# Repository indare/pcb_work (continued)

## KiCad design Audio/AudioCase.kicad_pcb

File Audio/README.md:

# Audio（AudioCase）

KiCad プロジェクトと関連ドキュメント。

## ドキュメント案内

| ファイル | 内容 |
|---|---|
| [MeasurementADC_STATUS.md](MeasurementADC_STATUS.md) | **現状・次作業・箱内配線方針**（まずここ） |
| [MeasurementADC_BRINGUP.md](MeasurementADC_BRINGUP.md) | 初号機の切り分けログ（履歴） |
| [MeasurementADC_ORDER.md](MeasurementADC_ORDER.md) | 発注・在庫 |
| [measurement_fw/README.md](measurement_fw/README.md) | 計測 Pico2 ファーム |
| [../Control/README.md](../Control/README.md) | Controll 親／子ファーム |
| [../README.md](../README.md) | リポジトリ全体・KiCad MCP |

## 階層シート

| シート | 役割 | いまの扱い |
|---|---|---|
| PowerModule | **DKMW20F-15** ±15 / ±660mA（1″×1″。TMR 6 は電流不足の次点）。計算メモ: [PowerModule_TEC3_REDESIGN.md](PowerModule_TEC3_REDESIGN.md) | 箱に入れる |
| AmpModule | NE5532 Amp（×10 想定）。AMP401 は DIP-8 ソケット | ラインアウト（J11）。ADC へは AdcBuffer 経由 |
| AdcBuffer | ゲイン1バッファ。実装は **OPA1652AID-DIP**（共立 Q5M411） | Amp L/R_OUT → MeasurementADC AUDIO |
| HeadphoneBuffer | ゲイン1電流バッファ。実装は **NJM4556A**（DIP-8 ソケット） | SW101 PHONE → パッド → RV101 → バッファ → J103 |
| Controll | CH1–10 リレー（親＋子） | 実機では外している |
| MeasurementADC | 計測＋LCD | 初号応急配線で稼働 |
| EQModule | EQ | 今号では使わない |
| RVConvert | RV 変換 | 箱計画に含むかは別途 |

## 出力切り替えとヘッドホン出力

SW101（DP3T）で Amp 出力の行き先を選ぶ。中央位置はミュート。

- PHONE: `SW101` → 固定パッド `R102/R101`（L）`R104/R103`（R）→ `RV101` A50k デュアル → `HeadphoneBuffer`（`R901/R903` 10Ω → `C901/C902` 470µF）→ `J103`
- LINE: `SW101` → `RV102` A50k デュアル → `J104`
- ADC への分岐はスイッチより手前なので、切り替え位置に関係なく測定できる

固定パッドは 8.2kΩ 直列＋910Ω 並列で約 −20dB。±15V・ゲイン1では最大出力がヘッドホンに対して過大で、
ボリュームが回転下端だけで使われてしまうため入れている。不要なら直列を 0Ω、並列を未実装にすればバイパスできる。
直列と並列の位置を取り違えると分圧にならず減衰が効かないので、必ず 8.2kΩ をスイッチ側の直列、910Ω を
ポット側から GND へ落とす並列にする。

**`RV101` はバッファより前**に置く。50kΩ のポットを 32Ω のヘッドホンより後ろに置くと、
ワイパー出力インピーダンス（中点で最大約 12.5kΩ）に対して負荷が軽すぎて −50dB 級まで落ち、
回転上端の数度だけで音が出るうえヘッドホン電流が抵抗体を流れる。

`C901/C902` は 470µF の**無極性（バイポーラ）**電解。両電源で出力の直流はほぼ 0V なので極性品は使わない。
故障時にヘッドホンへ ±15V が出るのを防ぐのと、電源投入時のポップ抑制が目的。
`R902/R904` 100kΩ はヘッドホン未接続時に出力ノードを確定させるブリード。

### SW101 はパネル実装（基板側は 2x04 ヘッダ）

KiCad 標準ライブラリに 2P3T（8ピン）のフットプリントが無く、選択機はパネルから操作する部品なので、
基板側は `PinHeader_2x04_P2.54mm_Vertical` にしてパネル実装の 2P3T スイッチへリード線で引く。
`SW_DIP_SPSTx04` 系は 8 パッドあるが独立 4 回路でピン機能が違うため流用しない。

| ヘッダピン | スイッチ端子 | つながる先 |
|---|---|---|
| 3 | L 極 コモン | Amp L 出力（ADC への分岐と共通） |
| 1 | L PHONE | 固定パッド `R102` → `RV101` |
| 2 | L MUTE | 未接続 |
| 4 | L LINE | `RV102` |
| 7 | R 極 コモン | Amp R 出力 |
| 5 | R PHONE | 固定パッド `R104` → `RV101` |
| 6 | R MUTE | 未接続 |
| 8 | R LINE | `RV102` |

## AdcBuffer の入力極性

`AMP801` は**上下反転で描いてある**（− 入力が上、+ 入力が下）。信号は `R804/R809` 0Ω で **+ 入力**へ入り、
`R805/R810` 100kΩ が + 入力のバイアスプルダウン、帰還は `R801/R806` 0Ω で **− 入力**へ戻り、
`R803/R808` 10kΩ が − 入力の Rg。Rf=0Ω なのでゲインは 1。

反転を戻して + と − を入れ替えると帰還が + 入力に回って正帰還になり、出力が電源レールに張り付く。
シンボルの向きだけで極性が決まるので、このシートを編集したら `Net-(AMP801A-+)` に `R804`/`R805` が、
`Net-(AMP801A--)` に `R801`/`R803` が入っていることをネットリストで確認する。

## オペアンプソケットの差し替え

3 か所すべて DIP-8 ソケットだが、役割が違うので入れられる品種が違う。**取り違えると壊す。**  
手持ち在庫の一覧は **[OPAMP_INVENTORY.md](OPAMP_INVENTORY.md)**。

| ソケット | 役割 | 標準 | 差し替え | 制約 |
|---|---|---|---|---|
| `AMP401`（AmpModule） | 電圧増幅 ×10（プリアンプ） | NE5532 | 手持ち DIP／DIP 化モジュール（在庫表） | 高速石は安定性注意。SOIC 単体は不可 |
| `AMP801`（AdcBuffer） | 測定系ゲイン1バッファ | OPA1652AID-DIP | 原則固定 | 測定の基準。ここを動かすと比較の土台が動く |
| `AMP901`（HeadphoneBuffer） | ヘッドホン電流ドライバ | NJM4556A | **不可** | 32Ω 直接駆動が必要。電圧アンプ系は電流不足 |

`AMP401` の出力は AdcBuffer 経由で測定 ADC にも、SW101 経由でヘッドホン／ラインにも行く。
つまりここを差し替えると、聴いている音と測っている波形が同じ変化を受ける。比較実験はこのソケットで行う。

## 分割 Gerber

`split/Gerber/` — `01_main` … `06_measurement_adc`。再生成は `scripts/regenerate_split_gerbers.py`。

## S式の健全性チェック

回路図・基板ファイルをテキスト編集したら `python3 scripts/check_sexpr.py -q .` で括弧の対応を確認する。
既知の壊れ方（`property` の閉じ括弧が早い）は `--fix` で直せる。手順は [`.cursor/rules/kicad-sexpr-integrity.mdc`](../.cursor/rules/kicad-sexpr-integrity.mdc)。

コミット時にも同じ検査が走る。クローン直後は一度だけ有効化が必要。

```bash
git config core.hooksPath .githooks
```

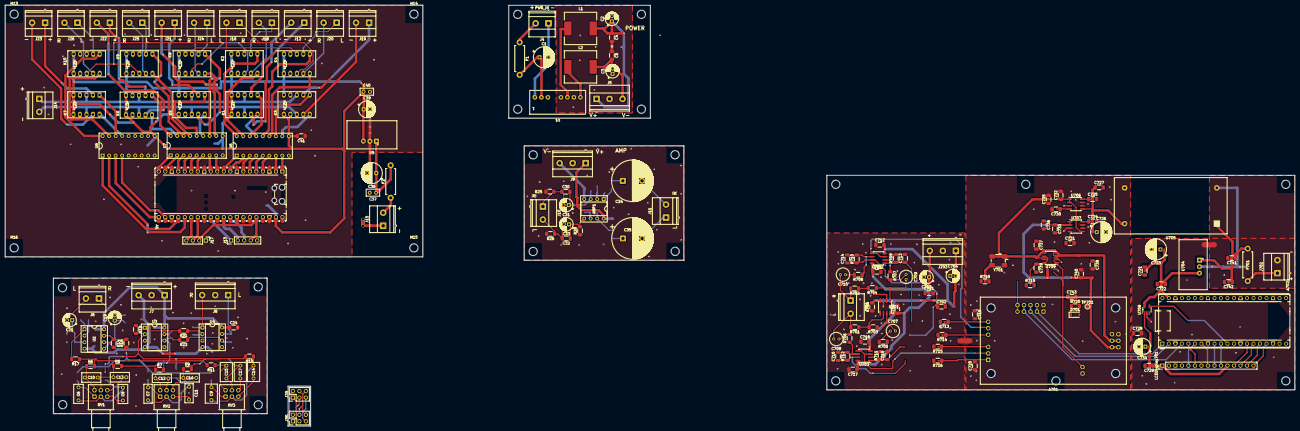
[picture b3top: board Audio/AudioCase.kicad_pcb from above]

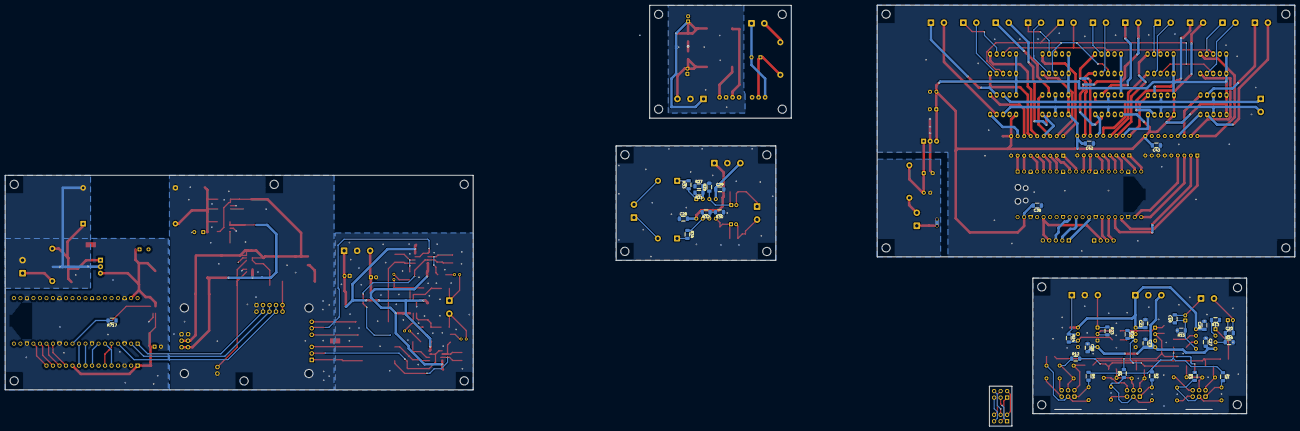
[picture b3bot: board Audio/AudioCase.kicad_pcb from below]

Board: 2 copper layers, 503.2 x 164.2 mm, 236 parts (32 on the bottom side), 185 nets.

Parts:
A1: RaspberryPi_Pico; RaspberryPi_Pico_Common_Unspecified
A701: ADC1804_F_MODULE; ADC1804_F_KYOHRITSU_56x33mm
A702: Pico2; RaspberryPi_Pico_Common_THT
AMP1: NE5532; DIP-8_W7.62mm_Socket
C1, C36: 47μF; CP_Radial_D8.0mm_P3.50mm
C2, C3: 4.7μF; CP_Radial_D5.0mm_P2.00mm
C4, C5, C18, C20, C22, C23, C24, C25, C26, C27, C28, C29, C30, C32, C38, C41, C42, C43: 0.1μF; C_1206_3216Metric_Pad1.33x1.80mm_HandSolder
C6, C8, C10, C13: 0.047μF; C_Rect_L7.2mm_W3.5mm_P5.00mm_FKS2_FKP2_MKS2_MKP2
C7, C11, C12, C16: 0.01uF; C_Rect_L7.2mm_W3.0mm_P5.00mm_FKS2_FKP2_MKS2_MKP2
C9, C14, C15, C17: 2200pF; C_Rect_L7.2mm_W4.5mm_P5.00mm_FKS2_FKP2_MKS2_MKP2
C19, C21, C31, C33: 10μF; CP_Radial_D5.0mm_P2.00mm
C34, C35: 470μF; CP_Radial_D16.0mm_P7.50mm
C37, C40: 0.1μF; C_Disc_D5.0mm_W2.5mm_P2.50mm
C39: 100μF; CP_Radial_D6.3mm_P2.50mm
C701, C702, C705, C706, C711, C712, C717, C718, C719, C720, C721, C722, C725, C727, C729, C730, C733, C740, C741, C743: 100nF; C_1206_3216Metric_Pad1.33x1.80mm_HandSolder
C703, C704: 10uF 50V; CP_Radial_D5.0mm_P2.00mm
C707, C708, C709, C710: 10uF 25V NP; C_Radial_D5.0mm_H7.0mm_P2.00mm
C713, C714, C715, C716: 1.8nF C0G; C_1206_3216Metric_Pad1.33x1.80mm_HandSolder
C723: 47uF 35V; CP_Radial_D8.0mm_P3.50mm
C724, C728, C739: 10uF; C_1206_3216Metric_Pad1.33x1.80mm_HandSolder
C726: 47uF; CP_Radial_D8.0mm_P3.50mm
C731, C732, C738: 10uF 16V X7R; C_1206_3216Metric_Pad1.33x1.80mm_HandSolder
C734: 22uF; CP_Radial_D6.3mm_P2.50mm
C735, C736, C742: 10nF; C_1206_3216Metric_Pad1.33x1.80mm_HandSolder
C737: 10uF 10V X7R; C_1206_3216Metric_Pad1.33x1.80mm_HandSolder
D701: RB160M-30; D_SOD-123
F1, F2: 1A; R_Axial_DIN0411_L9.9mm_D3.6mm_P12.70mm_Horizontal
F701: Fuse; R_Axial_DIN0411_L9.9mm_D3.6mm_P12.70mm_Horizontal
H1, H2, H3, H4, H5, H6, H7, H8, H9, H10, H11, H11#2, H11#3, H11#4, H11#5, H11#6, H11#7, H12, H13, H14, H15, H16: MountingHole; MountingHole_3.2mm_M3
J4: PWR_IN; TerminalBlock_Phoenix_MKDS-1,5-2_1x02_P5.00mm_Horizontal
J5: PWR_OUT; TerminalBlock_Phoenix_MKDS-1,5-3-5.08_1x03_P5.08mm_Horizont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
J6: AUX_IN; TerminalBlock_Phoenix_MKDS-1,5-2-5.08_1x02_P5.08mm_Horizont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
J7: V_IN; TerminalBlock_Phoenix_MKDS-1,5-3-5.08_1x03_P5.08mm_Horizont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
J8: AUX_OUT; TerminalBlock_Phoenix_MKDS-1,5-3-5.08_1x03_P5.08mm_Horizont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
J9: AMP_PWR; TerminalBlock_Phoenix_MKDS-1,5-3-5.08_1x03_P5.08mm_Horizont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
J10: AMP_AUX_IN; TerminalBlock_Phoenix_MKDS-1,5-2-5.08_1x02_P5.08mm_Horizont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
J11: AMP_AUX_OUT; TerminalBlock_Phoenix_MKDS-1,5-2-5.08_1x02_P5.08mm_Horizont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
J12: AMP1_PWR; TerminalBlock_Phoenix_MKDS-1,5-2-5.08_1x02_P5.08mm_Horizont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
J13: ROTARY_SW; PinHeader_1x05_P2.54mm_Vertical
J14: AMP_PWR_IN; TerminalBlock_Phoenix_MKDS-1,5-2-5.08_1x02_P5.08mm_Horizont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
J15: PD_IN; TerminalBlock_Phoenix_MKDS-1,5-2-5.08_1x02_P5.08mm_Horizont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
J16: AUDIO_IN; TerminalBlock_Phoenix_MKDS-1,5-2-5.08_1x02_P5.08mm_Horizont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
J17: OLED_PIN; PinHeader_1x04_P2.54mm_Vertical
J18: AMP1_LR; TerminalBlock_Phoenix_MKDS-1,5-2-5.08_1x02_P5.08mm_Horizont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
J19: AMP2_PWR; TerminalBlock_Phoenix_MKDS-1,5-2-5.08_1x02_P5.08mm_Horizont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
J20: AMP2_LR; TerminalBlock_Phoenix_MKDS-1,5-2-5.08_1x02_P5.08mm_Horizont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
J21: AMP3_PWR; TerminalBlock_Phoenix_MKDS-1,5-2-5.08_1x02_P5.08mm_Horizont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
J22: AMP4_PWR; TerminalBlock_Phoenix_MKDS-1,5-2-5.08_1x02_P5.08mm_Horizont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
J23: AMP5_PWR; TerminalBlock_Phoenix_MKDS-1,5-2-5.08_1x02_P5.08mm_Horizont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
J24: AMP3_LR; TerminalBlock_Phoenix_MKDS-1,5-2-5.08_1x02_P5.08mm_Horizont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
J25: AMP4_LR; TerminalBlock_Phoenix_MKDS-1,5-2-5.08_1x02_P5.08mm_Horizont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
J26: AMP5_LR; TerminalBlock_Phoenix_MKDS-1,5-2-5.08_1x02_P5.08mm_Horizont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
J29, J30: Conn_01x06_Pin; PinHeader_2x03_P2.54mm_Vertical
J701: AUDIO; TerminalBlock_Phoenix_MKDS-1,5-2-5.08_1x02_P5.08mm_Horizont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
J702: V_IN; TerminalBlock_Phoenix_MKDS-1,5-2-5.08_1x02_P5.08mm_Horizont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
J703: 15_V_IN; TerminalBlock_Phoenix_MKDS-1,5-3-5.08_1x03_P5.08mm_Horizont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
K1, K2, K3, K4, K5, K6, K7, K8, K9, K10: AZ850P2-x; Relay_DPDT_FRT5
L1, L2: L; L_12x12mm_H8mm
LCDDisplay701: WAVESHARE-29318; PinHeader_1x15_P2.54mm_Vertical
NT1: NetTie_2; NetTie-2_THT_Pad1.0mm
NT701: A_GND-ADC_GND; NetTie-2_SMD_Pad2.0mm
NT702: ADC_GND_IN-D_GND; NetTie-2_SMD_Pad2.0mm
R1, R2, R3, R4, R5, R6, R7, R8, R9, R10, R11, R12: 10K; R_1206_3216Metric_Pad1.30x1.75mm_HandSolder
R13, R14: 0Ω; R_1206_3216Metric_Pad1.30x1.75mm_HandSolder
R15, R16: 47kΩ; R_1206_3216Metric_Pad1.30x1.75mm_HandSolder
R17, R18, R33, R34: 47Ω; R_1206_3216Metric_Pad1.30x1.75mm_HandSolder
R19, R20, R27, R28, R29, R30: 10KΩ; R_1206_3216Metric_Pad1.30x1.75mm_HandSolder
R21, R22, R23, R24: 22KΩ; R_1206_3216Metric_Pad1.30x1.75mm_HandSolder
R25, R26: 220KΩ; R_1206_3216Metric_Pad1.30x1.75mm_HandSolder
R31, R32: 47KΩ; R_1206_3216Metric_Pad1.30x1.75mm_HandSolder
R701, R702, R703, R704: 4.7k 0.1%; R_1206_3216Metric_Pad1.30x1.75mm_HandSolder
R705, R706, R707, R708: 3.3k 0.1%; R_1206_3216Metric_Pad1.30x1.75mm_HandSolder
R709, R710, R711, R712: 1k 0.1%; R_1206_3216Metric_Pad1.30x1.75mm_HandSolder
R713, R714, R715, R716: 47; R_1206_3216Metric_Pad1.30x1.75mm_HandSolder
R717: 100k; R_1206_3216Metric_Pad1.30x1.75mm_HandSolder
R718: 33; R_1206_3216Metric_Pad1.30x1.75mm_HandSolder
R719: 10k; R_1206_3216Metric_Pad1.30x1.75mm_HandSolder
R720: 1k; R_1206_3216Metric_Pad1.30x1.75mm_HandSolder
RV1, RV2, RV3: B100k_Dual; Potentiometer_Alps_RK097_Dual_Horizontal
TP701: ADC_MCLK; TestPoint_Pad_D1.5mm
U1: MCW03; MCW03-12D15_SIP7_THT
U2, U3, U4: NJM4558; DIP-8_W7.62mm_Socket
U5, U704: BP5293-50; BP5293-50_ROHM_SIP-3
U6, U7, U8: ULN2803A; ULN2803A_DIP-18_W7.62mm
U701, U702, U703: OPA1656; SOIC-8_3.9x4.9mm_P1.27mm
U705: MBC2596-01; MBC2596-01_TAEJIN_43x21mm
U706: LT1763-3.3; SOIC-8_3.9x4.9mm_P1.27mm
U707: LT1763-5; SOIC-8_3.9x4.9mm_P1.27mm
U708: XC8107AC20MR-G; SOT-23-5_HandSoldering
U709: TPS3307-33; SOIC-8_3.9x4.9mm_P1.27mm
Y701: ASFL1-12.288MHZ-EC-T; Oscillator_SMD_Abracon_ASFL-4Pin_5.0x3.2mm_HandSoldering

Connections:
/AmpModule/L_IN: C32.2, C33.2, J10.2, R26.1
/AmpModule/R_IN: C30.2, C31.2, J10.1, R25.1
/AmpModule/V+_IN: AMP1.8 (V+), C28.2, J9.1
/AmpModule/V-_IN: AMP1.4 (V-), C29.1, J9.3
/Controll/3V3: A1.36 (3V3), J13.4, J17.2
/Controll/5V_+: A1.39 (VSYS), C38.2, C39.1, C40.1, C41.2, C42.2, C43.2, K1.1, K1.10, K2.1, K2.10, K3.1, K3.10, K4.1, K4.10, K5.1, K5.10, K6.1, K6.10, K7.1, K7.10, K8.1, K8.10, K9.1, K9.10, K10.1, K10.10, U5.3 (VOUT), U6.10 (COM), U7.10 (COM), U8.10 (COM)
/Controll/+15_IN: C723.1, C724.1, C725.1, F1.1, F2.1, F701.2, J4.2, J15.2, U704.1 (VIN), U705.1 (IN+)
/Controll/AMP_1_L_OUT: J18.1, K2.7
/Controll/AMP_1_R_OUT: J18.2, K2.4
/Controll/AMP_1_V+_OUT: J12.1, K1.7
/Controll/AMP_1_V-_OUT: J12.2, K1.4
/Controll/AMP_2_L_OUT: J20.1, K4.7
/Controll/AMP_2_R_OUT: J20.2, K4.4
/Controll/AMP_2_V+_OUT: J19.1, K3.7
/Controll/AMP_2_V-_OUT: J19.2, K3.4
/Controll/AMP_3_L_OUT: J24.1, K8.7
/Controll/AMP_3_R_OUT: J24.2, K8.4
/Controll/AMP_3_V+_OUT: J21.1, K5.7
/Controll/AMP_3_V-_OUT: J21.2, K5.4
/Controll/AMP_4_L_OUT: J25.1, K9.7
/Controll/AMP_4_R_OUT: J25.2, K9.4
/Controll/AMP_4_V+_OUT: J22.1, K6.7
/Controll/AMP_4_V-_OUT: J22.2, K6.4
/Controll/AMP_5_L_OUT: J26.1, K10.7
/Controll/AMP_5_R_OUT: J26.2, K10.4
/Controll/AMP_5_V+_OUT: J23.1, K7.7
/Controll/AMP_5_V-_OUT: J23.2, K7.4
/Controll/AMP_V+_IN: C2.1, C4.1, C22.1, C24.1, C26.1, C701.1, C703.1, C705.1, C711.1, C717.1, J5.1, J7.1, J14.1, J703.3, K1.8, K3.8, K5.8, K6.8, K7.8, L1.1, U2.8 (V+), U3.8 (V+), U4.8 (V+), U701.8 (V+), U702.8 (V+), U703.8 (V+)
/Controll/AMP_V-_IN: C3.2, C5.2, C23.2, C25.2, C27.2, C702.2, C704.2, C706.2, C712.2, C718.2, J5.3, J7.3, J14.2, J703.1, K1.3, K3.3, K5.3, K6.3, K7.3, L2.2, U2.4 (V-), U3.4 (V-), U4.4 (V-), U701.4 (V-), U702.4 (V-), U703.4 (V-)
/Controll/AUDIO_RESET_GPIO_1: A1.2 (GPIO1), U6.7 (I7)
/Controll/AUDIO_RESET_GPIO_2: A1.7 (GPIO5), U6.3 (I3)
/Controll/AUDIO_RESET_GPIO_3: A1.12 (GPIO9), U7.7 (I7)
/Controll/AUDIO_RESET_GPIO_4: A1.17 (GPIO13), U7.3 (I3)
/Controll/AUDIO_RESET_GPIO_5: A1.24 (GPIO18), U8.1 (I1)
/Controll/AUDIO_RESET_RELAY_1: K2.6, U6.18 (O1)
/Controll/AUDIO_RESET_RELAY_2: K4.6, U6.14 (O5)
/Controll/AUDIO_RESET_RELAY_3: K8.6, U7.12 (O7)
/Controll/AUDIO_RESET_RELAY_4: K9.6, U7.16 (O3)
/Controll/AUDIO_RESET_RELAY_5: K10.6, U8.18 (O1)
/Controll/AUDIO_SET_GPIO_1: A1.1 (GPIO0), U6.8 (I8)
/Controll/AUDIO_SET_GPIO_2: A1.6 (GPIO4), U6.4 (I4)
/Controll/AUDIO_SET_GPIO_3: A1.11 (GPIO8), U7.8 (I8)
/Controll/AUDIO_SET_GPIO_4: A1.16 (GPIO12), U7.4 (I4)
/Controll/AUDIO_SET_GPIO_5: A1.25 (GPIO19), U8.2 (I2)
/Controll/AUDIO_SET_RELAY_1: K2.5, U6.17 (O2)
/Controll/AUDIO_SET_RELAY_2: K4.5, U6.13 (O6)
/Controll/AUDIO_SET_RELAY_3: K8.5, U7.11 (O8)
/Controll/AUDIO_SET_RELAY_4: K9.5, U7.15 (O4)
/Controll/AUDIO_SET_RELAY_5: K10.5, U8.17 (O2)
/Controll/CTRL_GND: A1.3 (GND), A1.8 (GND), A1.13 (GND), A1.18 (GND), A1.23 (GND), A1.28 (GND), A1.38 (GND), C36.2, C37.2, C38.1, C39.2, C40.2, C41.1, C42.1, C43.1, J13.5, J17.1, NT1.2, U5.2 (GND), U6.9 (GND), U7.9 (GND), U8.5 (I5), U8.6 (I6), U8.7 (I7), U8.8 (I8), U8.9 (GND)
/Controll/ENC_A: A1.29 (GPIO22), J13.1
/Controll/ENC_B: A1.31 (GPIO26_ADC0), J13.2
/Controll/ENC_SW: A1.32 (GPIO27_ADC1), J13.3
/Controll/L_IN: J8.1, J16.2, K2.8, K4.8, K8.8, K9.8, K10.8, R24.1, U4.7
/Controll/PWR_RESET_GPIO_1: A1.5 (GPIO3), U6.5 (I5)
/Controll/PWR_RESET_GPIO_2: A1.10 (GPIO7), U6.1 (I1)
/Controll/PWR_RESET_GPIO_3: A1.15 (GPIO11), U7.5 (I5)
/Controll/PWR_RESET_GPIO_4: A1.20 (GPIO15), U7.1 (I1)
/Controll/PWR_RESET_GPIO_5: A1.21 (GPIO16), U8.3 (I3)
/Controll/PWR_RESET_RELAY_1: K1.6, U6.16 (O3)
/Controll/PWR_RESET_RELAY_2: K3.6, U6.12 (O7)
/Controll/PWR_RESET_RELAY_3: K5.6, U7.14 (O5)
/Controll/PWR_RESET_RELAY_4: K6.6, U7.18 (O1)
/Controll/PWR_RESET_RELAY_5: K7.6, U8.16 (O3)
/Controll/PWR_SET_GPIO_1: A1.4 (GPIO2), U6.6 (I6)
/Controll/PWR_SET_GPIO_2: A1.9 (GPIO6), U6.2 (I2)
/Controll/PWR_SET_GPIO_3: A1.14 (GPIO10), U7.6 (I6)
/Controll/PWR_SET_GPIO_4: A1.19 (GPIO14), U7.2 (I2)
/Controll/PWR_SET_GPIO_5: A1.22 (GPIO17), U8.4 (I4)
/Controll/PWR_SET_RELAY_1: K1.5, U6.15 (O4)
/Controll/PWR_SET_RELAY_2: K3.5, U6.11 (O8)
/Controll/PWR_SET_RELAY_3: K5.5, U7.13 (O6)
/Controll/PWR_SET_RELAY_4: K6.5, U7.17 (O2)
/Controll/PWR_SET_RELAY_5: K7.5, U8.15 (O4)
/Controll/R_IN: J8.3, J16.1, K2.3, K4.3, K8.3, K9.3, K10.3, R23.1, U4.1
/Controll/SCL: A1.27 (GPIO21), J17.3
/Controll/SDA: A1.26 (GPIO20), J17.4
/EQModule/L_BAX_SUM: R8.2, R9.2, R12.2, R20.2, U3.6 (-)
/EQModule/L_BUFF: R6.2, R7.2, R11.2, R17.1
/EQModule/L_BUFF_IN: C20.1, C21.1, R16.1, U2.3 (+)
/EQModule/L_IN: C20.2, C21.2, J6.2
/EQModule/R_BAX_SUM: R3.2, R4.2, R10.2, R19.2, U3.2 (-)
/EQModule/R_BUFF: R1.1, R2.1, R5.1, R18.1
/EQModule/R_BUFF_IN: C18.1, C19.1, R15.1, U2.5 (+)
/EQModule/R_IN: C18.2, C19.2, J6.1
/MeasurementADC/+3V3_A: A701.13 (+3V3), C722.2, C737.1, C740.1, C742.2, C743.1, R719.1, U706.1 (OUT), U706.2 (SENSE), U707.5 (SHDN), U709.2 (SENSE2), U709.3 (SENSE3), U709.8 (VDD), Y701.1 (ST), Y701.4 (VDD)
/MeasurementADC/+5V_A: A701.12 (+5V), C721.1, C738.1, C741.1, U707.1 (OUT), U707.2 (SENSE), U709.1 (SENSE1)
/MeasurementADC/+5V_D: C726.1, C727.1, C728.1, D701.2 (A), U704.3 (VOUT), U708.5 (VIN)
/MeasurementADC/ADC_BCK: A701.9 (BCK), A702.2 (GPIO1)
/MeasurementADC/ADC_DATA: A701.10 (DATA), A702.1 (GPIO0)
/MeasurementADC/ADC_GND: A701.14 (GND), C719.1, C720.1, C721.2, C722.1, C729.2, C730.2, C731.2, C732.2, C735.2, C736.2, C737.2, C738.2, C740.2, C741.2, C742.1, C743.2, NT701.1, U705.4 (OUT-), U706.3 (GND), U706.6 (GND), U706.7 (GND), U707.3 (GND), U707.6 (GND), U707.7 (GND), U709.4 (GND), Y701.2 (GND)
/MeasurementADC/ADC_GND_IN: C1.2, C723.2, C724.2, C725.2, J4.1, J15.1, J702.2, NT1.1, NT702.1, U1.1 (GND), U704.2 (GND), U705.2 (IN-)
/MeasurementADC/ADC_LRCK: A701.8 (LRCK), A702.4 (GPIO2)
/MeasurementADC/ADC_MCLK: A701.7 (SCKI), R718.2, R720.1, TP701.1 (1_1)
/MeasurementADC/ADC_nMR: A702.20 (GPIO15), U709.7 (~MR)
/MeasurementADC/ADC_nRST: A701.11 (RST), R719.2, U709.5 (~RESET)
/MeasurementADC/AUDIO_L_IN: C35.2, C708.2, J11.1, J701.2, R701.2
/MeasurementADC/AUDIO_R_IN: C34.2, C710.2, J11.2, J701.1, R702.2
/MeasurementADC/D_GND: A702.3 (GND), A702.8 (GND), A702.13 (GND), A702.18 (GND), A702.23 (GND), A702.28 (GND), A702.38 (GND), C726.2, C727.2, C728.2, C733.1, C734.2, C739.2, LCDDisplay701.3 (GND), NT702.2, R717.2, U708.2 (VSS)
/MeasurementADC/LCD_CS: A702.7 (GPIO5), LCDDisplay701.8 (LCD_CS)
/MeasurementADC/LCD_DC: A702.9 (GPIO6), LCDDisplay701.9 (LCD_DC)
/MeasurementADC/LCD_EN: A702.11 (GPIO8), R717.1, U708.4 (CE)
/MeasurementADC/LCD_MOSI: A702.25 (GPIO19), LCDDisplay701.5 (MOSI)
/MeasurementADC/LCD_RST: A702.10 (GPIO7), LCDDisplay701.10 (LCD_RST)
/MeasurementADC/LCD_SCK: A702.24 (GPIO18), LCDDisplay701.6 (SCLK)
/MeasurementADC/LCD_VCC: C733.2, C734.1, C739.1, LCDDisplay701.1 (VCC), LCDDisplay701.11 (LCD_BL), U708.1 (VOUT)
/MeasurementADC/MCLK_SENSE: A702.12 (GPIO9), R720.2
/MeasurementADC/PICO_3V3: A702.30 (RUN), A702.35 (ADC_VREF), A702.36 (3V3), A702.37 (3V3_EN)
/MeasurementADC/TP_INT: A702.16 (GPIO12), LCDDisplay701.14 (TP_INT)
/MeasurementADC/TP_RST: A702.17 (GPIO13), LCDDisplay701.15 (TP_RST)
/MeasurementADC/TP_SCL: A702.15 (GPIO11), LCDDisplay701.13 (TP_SCL)
/MeasurementADC/TP_SDA: A702.14 (GPIO10), LCDDisplay701.12 (TP_SDA)
/MeasurementADC/VCOML: A701.2 (VCOML), C719.2, U703.3 (INA+), U703.5 (INB+)
/MeasurementADC/VCOMR: A701.5 (VCOMR), C720.2, U702.3 (INA+), U702.5 (INB+)
/MeasurementADC/VINL+: A701.1 (VINL+), R716.1
/MeasurementADC/VINL-: A701.3 (VINL-), R715.1
/MeasurementADC/VINR+: A701.6 (VINR+), R714.1
/MeasurementADC/VINR-: A701.4 (VINR-), R713.1
GND: C2.2, C3.1, C4.2, C5.1, C22.2, C23.1, C24.2, C25.1, C26.2, C27.1, C28.1, C29.2, C701.2, C702.1, C703.2, C704.1, C705.2, C706.1, C711.2, C712.1, C717.2, C718.1, J5.2, J7.2, J8.2, J9.2, J703.2, NT701.2, R15.2, R16.2, R25.2, R26.2, R27.1, R28.1, R29.2, R30.1, U1.7 (Common), U3.3 (+), U3.5 (+), U4.3 (+), U4.5 (+), U701.3 (INA+), U701.5 (INB+)
unnamed: A702.39 (VSYS), D701.1 (K)
unnamed: AMP1.1, R31.2, R33.1
unnamed: AMP1.7, R32.2, R34.1
unnamed: AMP1.3 (+), C30.1, C31.1, R29.1
unnamed: AMP1.2 (-), R27.2, R31.1
unnamed: AMP1.5 (+), C32.1, C33.1, R28.2
unnamed: AMP1.6 (-), R30.2, R32.1
unnamed: C6.1, R1.2, RV1.1
unnamed: C6.2, C8.1, R3.1, RV1.2
unnamed: C7.1, R2.2, RV2.1
unnamed: C8.2, RV1.3
unnamed: C9.1, R5.2, RV3.1
unnamed: C10.1, C13.2, R8.1, RV1.5
unnamed: C10.2, R6.1, RV1.4
unnamed: C7.2, C11.1, R4.1, RV2.2
unnamed: C11.2, RV2.3
unnamed: C12.1, C16.1, R9.1, RV2.5
unnamed: C12.2, R7.1, RV2.4
unnamed: C13.1, RV1.6
unnamed: C9.2, C14.1, R10.1, RV3.2
unnamed: C14.2, RV3.3
unnamed: C15.1, C17.1, R12.1, RV3.5
unnamed: C15.2, R11.1, RV3.4
unnamed: C16.2, RV2.6
unnamed: C17.2, RV3.6
unnamed: C34.1, R33.2
unnamed: C35.1, R34.2
unnamed: C707.1, R705.2
unnamed: C708.1, R706.2
unnamed: C709.1, R707.2
unnamed: C710.1, R708.2
unnamed: J29.1, J30.3
unnamed: J29.2, J30.2
unnamed: J29.3, J30.1
unnamed: J29.4, J30.6
unnamed: J29.5, J30.5
unnamed: J29.6, J30.4
unnamed: F701.1, J702.1
unnamed: R13.1, R17.2, U2.1
unnamed: R14.1, R18.2, U2.7
unnamed: R19.1, R21.2, U3.1
unnamed: R20.1, R22.2, U3.7
unnamed: C1.1, F1.2, U1.2 (+Vin)
unnamed: L1.2, U1.6 (+Vout)
unnamed: L2.1, U1.8 (-Vout)
unnamed: R13.2, U2.2 (-)
unnamed: R14.2, U2.6 (-)
unnamed: R21.1, R23.2, U4.2 (-)
unnamed: R22.1, R24.2, U4.6 (-)
unnamed: C36.1, C37.1, F2.2, U5.1 (VIN)
unnamed: R702.1, R704.2, U701.2 (INA-)
unnamed: C709.2, R704.1, U701.1 (OUTA)
unnamed: R701.1, R703.2, U701.6 (INB-)
unnamed: C707.2, R703.1, U701.7 (OUTB)
unnamed: C713.2, R707.1, R709.2, U702.2 (INA-)
unnamed: C713.1, R709.1, R713.2, U702.1 (OUTA)
unnamed: C714.2, R708.1, R710.2, U702.6 (INB-)
unnamed: C714.1, R710.1, R714.2, U702.7 (OUTB)
unnamed: C715.2, R705.1, R711.2, U703.2 (INA-)
unnamed: C715.1, R711.1, R715.2, U703.1 (OUTA)
unnamed: C716.2, R706.1, R712.2, U703.6 (INB-)
unnamed: C716.1, R712.1, R716.2, U703.7 (OUTB)
unnamed: C729.1, C730.1, C731.1, C732.1, U705.3 (OUT+), U706.5 (SHDN), U706.8 (IN), U707.8 (IN)
unnamed: C735.1, U706.4 (BYP)
unnamed: C736.1, U707.4 (BYP)
unnamed: R718.1, Y701.3 (OUT)

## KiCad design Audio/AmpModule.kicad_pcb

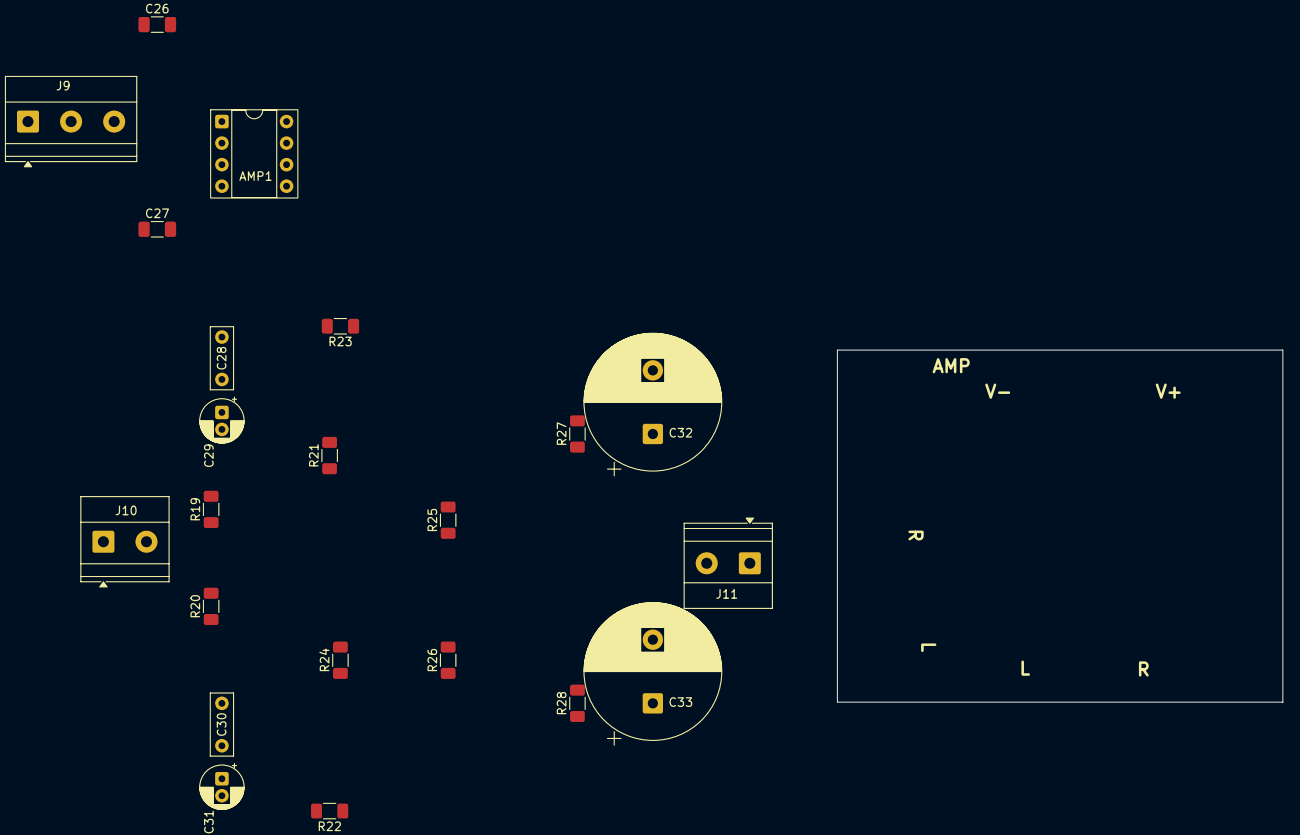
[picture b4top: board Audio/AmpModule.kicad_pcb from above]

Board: 2 copper layers, 52.5 x 41.5 mm, 26 parts (0 on the bottom side), 7 nets, no tracks yet.

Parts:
AMP1: NE5532; DIP-8_W7.62mm_Socket
C26, C27: 0.1μF; C_1206_3216Metric_Pad1.33x1.80mm_HandSolder
C28, C30: 0.1μF; C_Rect_L7.2mm_W2.5mm_P5.00mm_FKS2_FKP2_MKS2_MKP2
C29, C31: 10μF; CP_Radial_D5.0mm_P2.00mm
C32, C33: 470μF; CP_Radial_D16.0mm_P7.50mm
H9, H10, H11, H12: MountingHole; MountingHole_3.2mm_M3
J9: AMP_PWR; TerminalBlock_Phoenix_MKDS-1,5-3-5.08_1x03_P5.08mm_Horizont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
J10: AMP_AUX_IN; TerminalBlock_Phoenix_MKDS-1,5-2-5.08_1x02_P5.08mm_Horizont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
J11: AMP_AUX_OUT; TerminalBlock_Phoenix_MKDS-1,5-2-5.08_1x02_P5.08mm_Horizont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
R19, R20: 220KΩ; R_1206_3216Metric_Pad1.30x1.75mm_HandSolder
R21, R22, R23, R24: 10KΩ; R_1206_3216Metric_Pad1.30x1.75mm_HandSolder
R25, R26: 47KΩ; R_1206_3216Metric_Pad1.30x1.75mm_HandSolder
R27, R28: 47Ω; R_1206_3216Metric_Pad1.30x1.75mm_HandSolder

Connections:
/AmpModule/L_OUT: C32.2, C33.2
/Rotary_L_OUT: J10.2, J11.2
/Rotary_R_OUT: C28.2, C29.2, C30.2, C31.2, J10.1, J11.1
/Rotary_V+_OUT: AMP1.8 (V+), J9.1
/Rotary_V-_OUT: AMP1.4 (V-), J9.3
unnamed: AMP1.3 (+), C28.1, C29.1, C30.1, C31.1
unnamed: C32.1, C33.1

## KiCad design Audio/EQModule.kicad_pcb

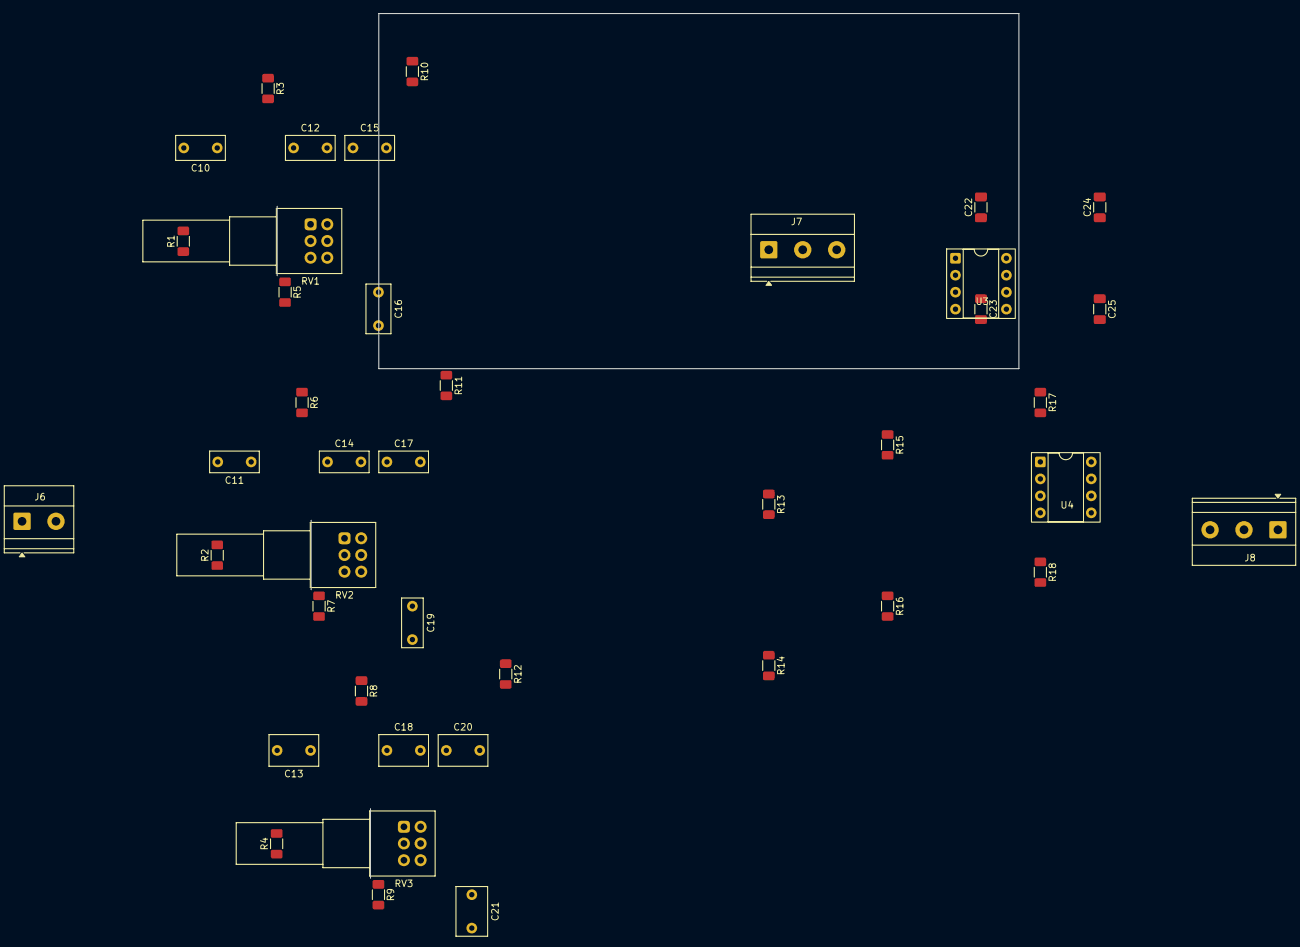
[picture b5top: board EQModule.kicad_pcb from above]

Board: 2 copper layers, 46 parts (0 on the bottom side), 9 nets, no tracks yet.

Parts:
C10, C12, C15, C16: 0.047μF; C_Rect_L7.2mm_W3.5mm_P5.00mm_FKS2_FKP2_MKS2_MKP2
C11, C14, C17, C19: 0.01uF; C_Rect_L7.2mm_W3.0mm_P5.00mm_FKS2_FKP2_MKS2_MKP2
C13, C18, C20, C21: 2200pF; C_Rect_L7.2mm_W4.5mm_P5.00mm_FKS2_FKP2_MKS2_MKP2
C22, C23, C24, C25: 0.1μF; C_1206_3216Metric_Pad1.33x1.80mm_HandSolder
H5, H6, H7, H8: MountingHole; MountingHole_3.2mm_M3
J6: AUX_IN; TerminalBlock_Phoenix_MKDS-1,5-2-5.08_1x02_P5.08mm_Horizont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
J7: V_IN; TerminalBlock_Phoenix_MKDS-1,5-3-5.08_1x03_P5.08mm_Horizont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
J8: AUX_OUT; TerminalBlock_Phoenix_MKDS-1,5-3-5.08_1x03_P5.08mm_Horizont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
R1, R2, R3, R4, R5, R6, R7, R8, R9, R10, R11, R12: 10K; R_1206_3216Metric_Pad1.30x1.75mm_HandSolder
R13, R14: 10KΩ; R_1206_3216Metric_Pad1.30x1.75mm_HandSolder
R15, R16, R17, R18: 22KΩ; R_1206_3216Metric_Pad1.30x1.75mm_HandSolder
RV1, RV2, RV3: B100k_Dual; Potentiometer_Alps_RK097_Dual_Horizontal
U3, U4: NJM4558; DIP-8_W7.62mm_Socket

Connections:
/Rotary_V+_OUT: J7.1, J8.1, U3.8 (V+), U4.8 (V+)
/Rotary_V-_OUT: J7.3, J8.3, U3.4 (V-), U4.4 (V-)
GND: J7.2, J8.2
unnamed: U3.1, U4.1
unnamed: U3.7, U4.7
unnamed: U3.3 (+), U4.3 (+)
unnamed: U3.2 (-), U4.2 (-)
unnamed: U3.5 (+), U4.5 (+)
unnamed: U3.6 (-), U4.6 (-)

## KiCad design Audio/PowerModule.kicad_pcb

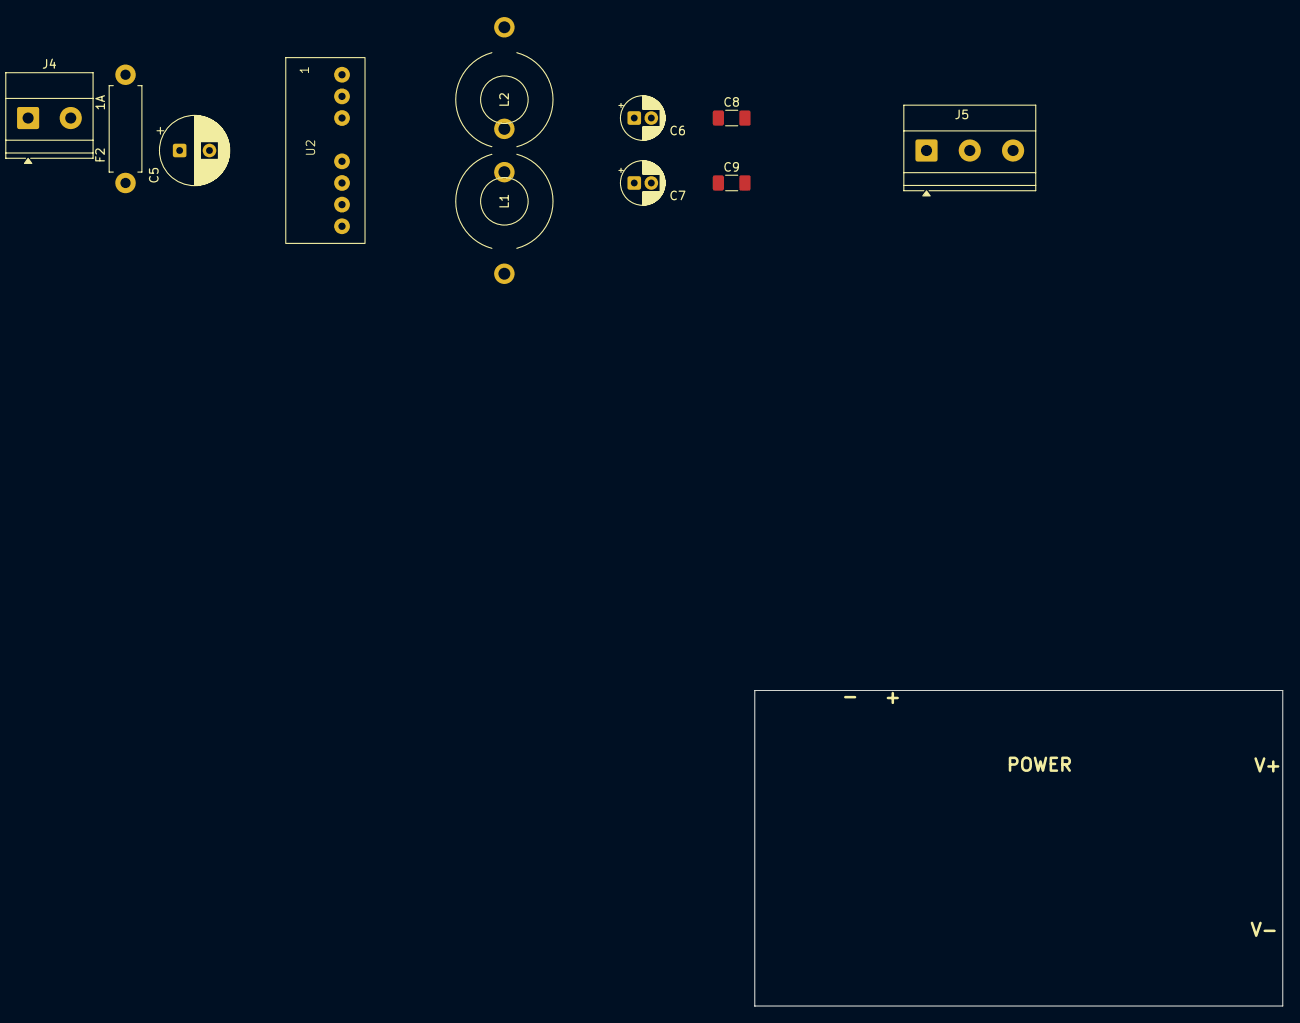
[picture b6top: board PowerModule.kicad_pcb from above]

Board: 2 copper layers, 62.0 x 37.0 mm, 15 parts (0 on the bottom side), 8 nets, no tracks yet.

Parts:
C5: 47μF; CP_Radial_D8.0mm_P3.50mm
C6, C7: 4.7μF; CP_Radial_D5.0mm_P2.00mm
C8, C9: 0.1μF; C_1206_3216Metric_Pad1.33x1.80mm_HandSolder
F2: 1A; R_Axial_DIN0411_L9.9mm_D3.6mm_P12.70mm_Horizontal
H1, H2, H3, H4: MountingHole; MountingHole_3.2mm_M3
J4: PWR_IN; TerminalBlock_Phoenix_MKDS-1,5-2_1x02_P5.00mm_Horizontal
J5: PWR_OUT; TerminalBlock_Phoenix_MKDS-1,5-3-5.08_1x03_P5.08mm_Horizont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
L1, L2: L; L_Toroid_Horizontal_D11.2mm_P17.00mm_Diameter12-5mm_Amidon-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
U2: MCW03-12D15_SIP7_THT

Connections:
/PowerModule/+15_IN: F2.1, J4.2
/PowerModule/PD_GND_IN: C5.2, J4.1, U2.1 (GND)
/Rotary_R_OUT: C6.2, C7.2
/Rotary_V-_IN: L1.2, L2.2
GND: J5.2, U2.7 (Common)
unnamed: C6.1, C7.1
unnamed: C5.1, F2.2, U2.2 (+Vin)
unnamed: L1.1, L2.1, U2.8 (-Vout)

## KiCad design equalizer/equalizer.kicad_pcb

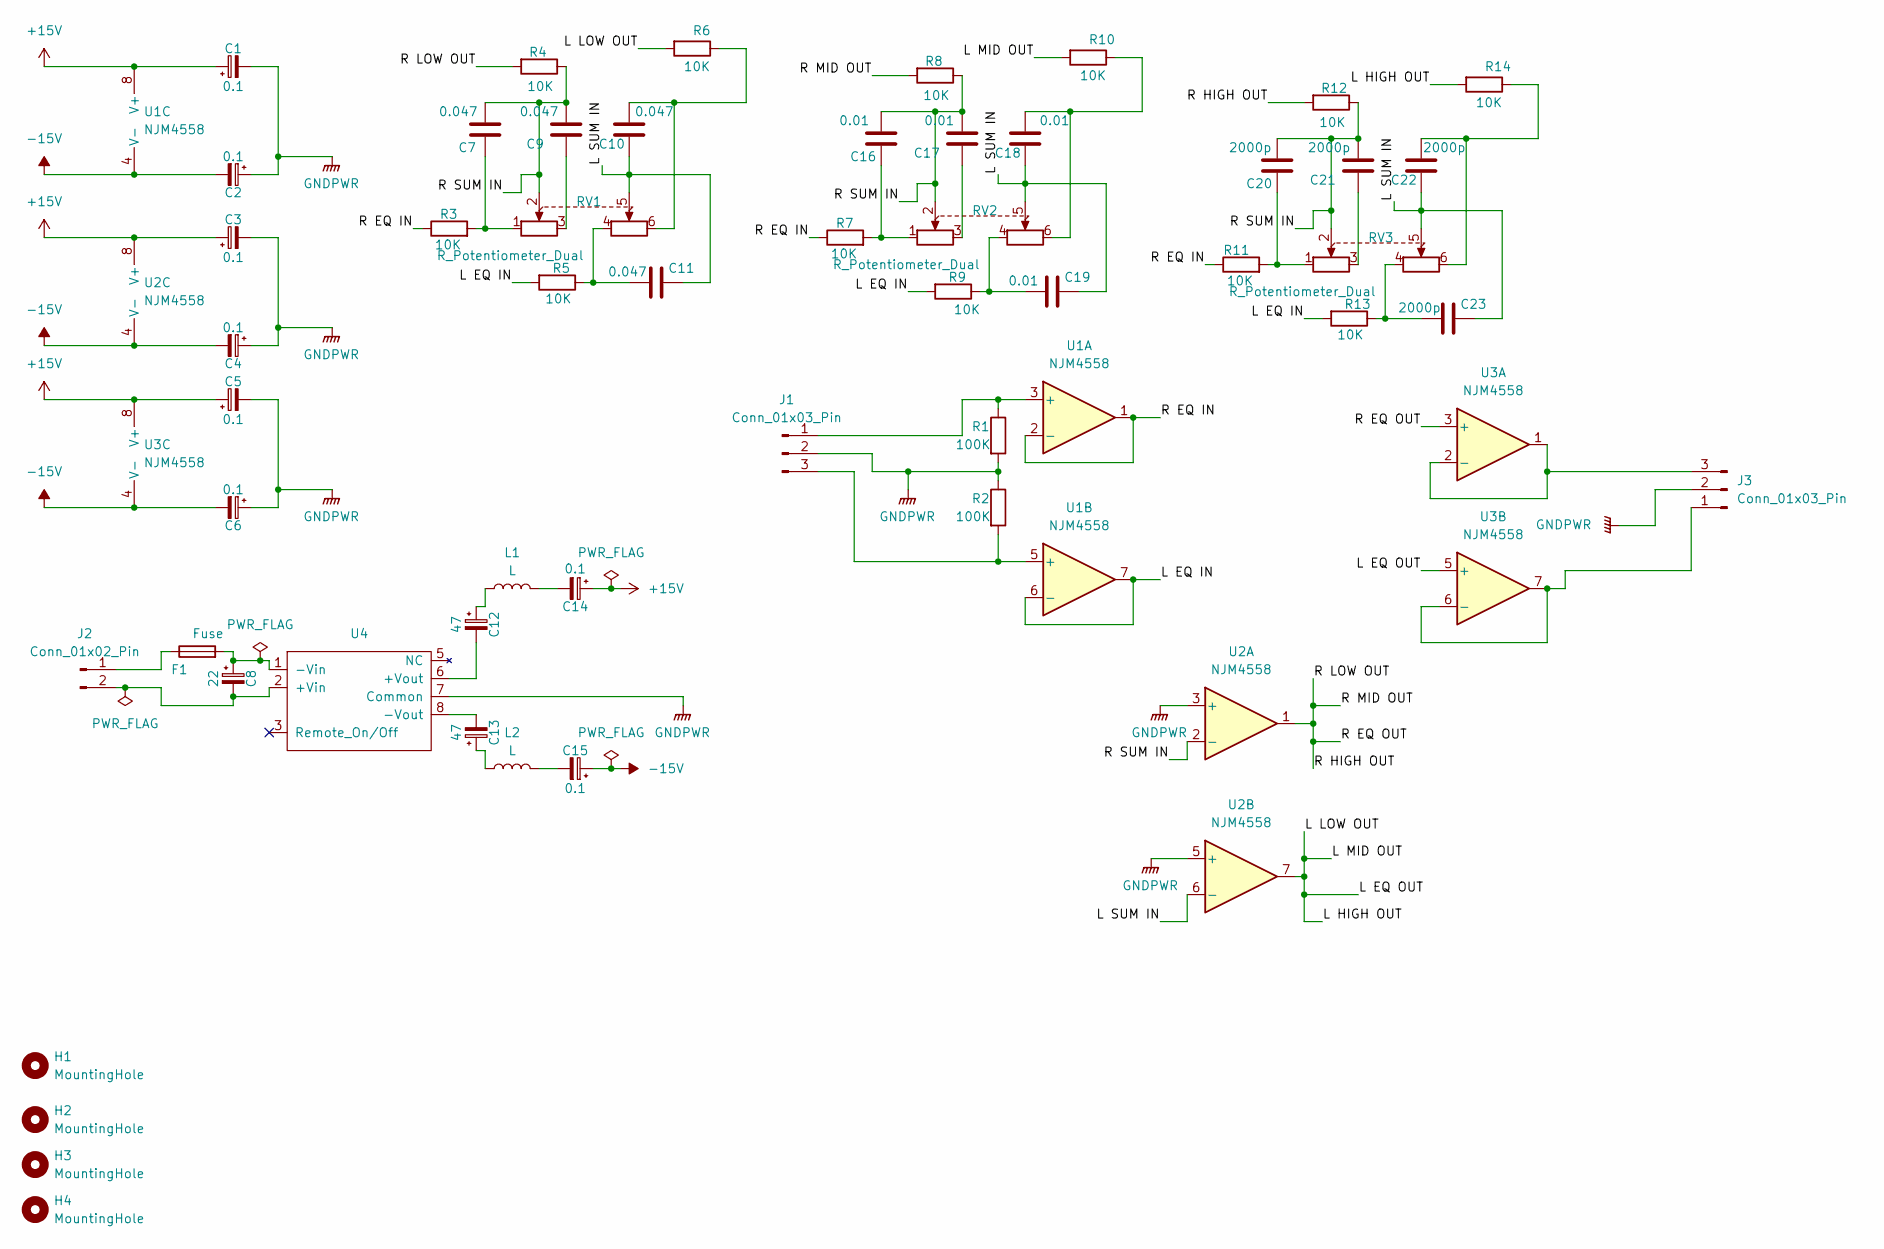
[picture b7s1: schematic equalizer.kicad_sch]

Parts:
C1, C2, C3, C4, C5, C6, C14, C15: 0.1; C_Disc_D5.0mm_W2.5mm_P2.50mm
C7, C9, C10, C11: 0.047; C_Rect_L13.0mm_W6.0mm_P10.00mm_FKS3_FKP3_MKS4
C8: 22; C_Disc_D5.0mm_W2.5mm_P2.50mm
C12, C13: 47; C_Disc_D5.0mm_W2.5mm_P2.50mm
C16, C17, C18, C19: 0.01; C_Rect_L13.0mm_W6.0mm_P10.00mm_FKS3_FKP3_MKS4
C20, C21, C22, C23: 2000p; C_Rect_L13.0mm_W6.0mm_P10.00mm_FKS3_FKP3_MKS4
F1: Fuse; R_Axial_DIN0411_L9.9mm_D3.6mm_P12.70mm_Horizontal
H1, H2, H3, H4: MountingHole; MountingHole_3.2mm_M3
J1, J3: Conn_01x03_Pin; TerminalBlock_Phoenix_MKDS-1,5-3_1x03_P5.00mm_Horizontal
J2: Conn_01x02_Pin; TerminalBlock_Phoenix_MKDS-1,5-2_1x02_P5.00mm_Horizontal
L1, L2: L; CP_Radial_D10.0mm_P5.00mm
R1, R2: 100K; R_Axial_DIN0207_L6.3mm_D2.5mm_P10.16mm_Horizontal
R3, R4, R5, R6, R7, R8, R9, R10, R11, R12, R13, R14: 10K; R_Axial_DIN0207_L6.3mm_D2.5mm_P10.16mm_Horizontal
RV1, RV2, RV3: R_Potentiometer_Dual; Potentiometer_Alps_RK09L_Double_Horizontal
U1, U2, U3: NJM4558; DIP-8_W7.62mm_Socket
U4: Converter_DCDC_TRACO_TMR4-xxxxWI_THT

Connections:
+15V: C1.1, C3.1, C5.1, C14.1, U1.8 (V+), U2.8 (V+), U3.8 (V+)
-15V: C2.2, C4.2, C6.2, C15.1, U1.4 (V-), U2.4 (V-), U3.4 (V-)
/L EQ IN: R5.2, R9.2, R13.2, U1.6 (-), U1.7
/L EQ OUT: R6.2, R10.2, R14.2, U2.7, U3.5 (+)
/L SUM IN: C10.2, C11.1, C18.2, C19.1, C22.2, C23.1, RV1.5, RV2.5, RV3.5, U2.6 (-)
/R EQ IN: R3.1, R7.1, R11.1, U1.1, U1.2 (-)
/R EQ OUT: R4.2, R8.2, R12.2, U2.1, U3.3 (+)
/R SUM IN: C7.2, C9.1, C16.2, C17.1, C20.2, C21.1, R4.1, R8.1, R12.1, RV1.2, RV2.2, RV3.2, U2.2 (-)
GNDPWR: C1.2, C2.1, C3.2, C4.1, C5.2, C6.1, J1.2, J3.2, R1.2, R2.1, U2.3 (+), U2.5 (+), U4.7 (Common)
unnamed: C7.1, R3.2, RV1.1
unnamed: C9.2, RV1.3
unnamed: C10.1, R6.1, RV1.6
unnamed: C11.2, R5.1, RV1.4
unnamed: C12.1, L1.1
unnamed: C13.1, L2.1
unnamed: C14.2, L1.2
unnamed: C15.2, L2.2
unnamed: C16.1, R7.2, RV2.1
unnamed: C17.2, RV2.3
unnamed: C18.1, R10.1, RV2.6
unnamed: C19.2, R9.1, RV2.4
unnamed: C20.1, R11.2, RV3.1
unnamed: C21.2, RV3.3
unnamed: C22.1, R14.1, RV3.6
unnamed: C23.2, R13.1, RV3.4
unnamed: J1.1, R1.1, U1.3 (+)
unnamed: J1.3, R2.2, U1.5 (+)
unnamed: F1.1, J2.1
unnamed: C8.2, J2.2, U4.2 (+Vin)
unnamed: J3.1, U3.6 (-), U3.7
unnamed: J3.3, U3.1, U3.2 (-)
unnamed: C12.2, U4.6 (+Vout)
unnamed: C8.1, F1.2, U4.1 (-Vin)
unnamed: C13.2, U4.8 (-Vout)

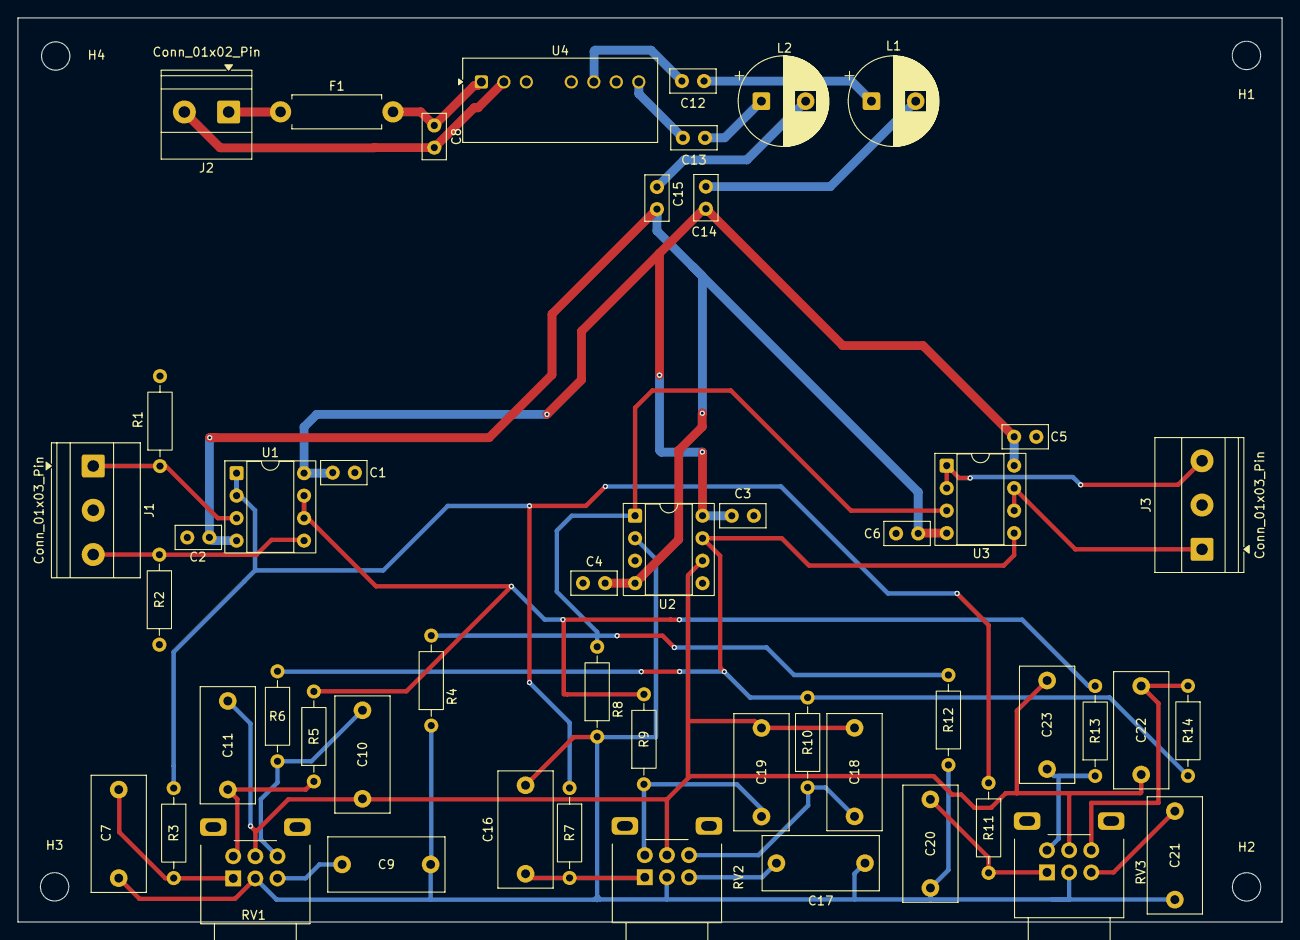
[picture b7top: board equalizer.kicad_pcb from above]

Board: 2 copper layers, 142.8 x 102.1 mm, 54 parts (0 on the bottom side), 34 nets.
